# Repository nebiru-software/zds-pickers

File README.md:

# zds-pickers 🎵

Picker controls that are common to ZendrumStudio apps - a React component library for MIDI/music applications.

## Overview

zds-pickers provides a comprehensive set of React components for building MIDI controller interfaces, music applications, and audio configuration UIs. The library focuses on picker-style controls that allow users to select values, notes, channels, and other musical parameters.

## Architecture

The library is organized into several key areas:

- **🎵 Music Components**: Piano interfaces, octave players, and audio providers
- **🎛️ Control Components**: Knobs, sliders, and interactive controls
- **🎯 Selection Components**: Dropdowns and pickers for various MIDI parameters
- **🔧 Utilities**: Shared components and helpers

## Key Features

- **TypeScript-first**: Full type safety with comprehensive interfaces
- **Audio Integration**: Built-in soundfont support for audio feedback
- **MIDI-Focused**: Components designed specifically for MIDI applications
- **Customizable**: Extensive theming and styling options
- **Accessible**: Keyboard navigation and screen reader support
- **Storybook Documentation**: Interactive component playground

## Quick Start

```bash
npm install zds-pickers react-select
```

Peer dependencies (`react`, `react-dom`, `react-select`, `classnames`, `zds-mappings`) must be installed in the host app. `react-select` was moved out of the package bundle in 4.1.x — add it explicitly if you use `Select`-based pickers.

```tsx
import { PianoPicker, KnobPicker, NotePicker } from 'zds-pickers'

function MyMIDIApp() {
  return (
    <div>
      <PianoPicker
        width={800}
        height={200}
        instrumentName="acoustic_grand_piano"
        onChange={(note) => console.log('Note played:', note)}
      />
      <KnobPicker
        label="Volume"
        min={0}
        max={127}
        value={64}
        onChange={(value) => console.log('Volume:', value)}
      />
    </div>
  )
}
```

## Component Documentation

**📚 All component examples, props, and usage patterns are documented in Storybook.**

Run `npm run sb` to access the interactive component playground with:
- Live examples of all components
- Interactive prop controls
- Multiple variants and states
- Copy-paste code snippets

### Available Components

**🎵 Music & Audio**
- `PianoPicker` - Full piano keyboard with soundfont integration
- `OctavePlayer` - Single octave piano interface
- `KeyPicker` - Octave-based MIDI note selection with highlighted key state

**🎛️ Controls**
- `KnobPicker` - Draggable knob with label and value display
- `ResponseCurvePicker` - Visual response curve selection
- `Knob` - Base knob component (from rotaryKnob)

**🎯 Selection**
- `NotePicker` - MIDI note selection with drum mapping support
- `ChannelPicker` - MIDI channel selection (1-16)
- `CCPicker` - MIDI Control Change number selection
- `StatusPicker` - MIDI status message selection
- `ChannelMappingPicker` - Channel mapping with drum kit presets
- `MappingPicker` - General mapping selection
- `PolarityPicker` - On/Off polarity selection
- `LatchPicker` - Latch mode selection
- `ValuePicker` - Generic value selection

**🔧 Utilities**
- `Select` - Generic select component with no-selection support
- `DefaultTooltip` - Tooltip component
- `SvgText` - SVG text rendering

## Audio Integration

The library includes `SoundfontProvider` for audio feedback:

```tsx
<SoundfontProvider
  audioContext={audioContext}
  instrumentName="acoustic_grand_piano"
  soundfont="MusyngKite"
  render={({ isLoading, playNote, stopNote }) => (
    <YourComponent
      playNote={playNote}
      stopNote={stopNote}
      disabled={isLoading}
    />
  )}
/>
```

## Development

### Setup
```bash
npm install
npm run dev          # Start Vite dev server
npm run sb           # Start Storybook
npm run build        # Build library
npm run lint         # Run Biome linter
```

### Storybook
**Primary documentation and testing environment** - all component examples, props, and usage patterns:
```bash
npm run sb
# Opens http://localhost:6006
```

Storybook serves as the single source of truth for:
- Component examples and variants
- Interactive prop controls
- Live code snippets
- Visual testing and development

### Building
The library builds to both CommonJS and ES modules:
- `dist/index.cjs.js` - CommonJS build
- `dist/index.es.js` - ES module build
- `dist/types/` - TypeScript definitions

## Peer dependencies

Install these in your application (they are not bundled with `zds-pickers`):

| Package | Version |
|---------|---------|
| `react` | >=18.0.0 |
| `react-dom` | >=18.0.0 |
| `react-select` | >=5.10.0 |
| `classnames` | >=2.5.1 |
| `zds-mappings` | 1.4.9 |

## Dependencies

### Core Dependencies
- **React 18+** - Component framework (peer)
- **TypeScript** - Type safety
- **D3.js** - Drag interactions and scaling
- **soundfont-player** - Audio playback
- **zds-react-piano** - Piano component
- **zds-mappings** - MIDI mappings

### Development Dependencies
- **Vite** - Build tool
- **Storybook** - Component documentation
- **Biome** - Linting and formatting
- **Tonal** - Music theory utilities

## Type Safety

All components are fully typed with TypeScript. Key interfaces:

```tsx
// Common picker props
interface BasePickerProps {
  disabled?: boolean
  label?: string
  shrinkLabel?: boolean
  value?: number | string
  onChange?: (value: number | string) => void
}

// Audio provider props
interface SoundfontProviderProps {
  audioContext: AudioContext
  instrumentName?: Soundfont.InstrumentName
  soundfont?: 'MusyngKite' | 'FluidR3_GM'
  render: (props: AudioRenderProps) => React.ReactNode
}
```

## Contributing

This is a single-developer library. The codebase follows these patterns:

- **Functional components** with hooks
- **TypeScript interfaces** for all props
- **Storybook stories** for each component
- **Biome** for consistent formatting
- **Modular exports** from index.ts

## License

MIT License - see LICENSE file for details.

## Repository

- **GitHub**: https://github.com/dkadrios/zds-pickers
- **NPM**: https://www.npmjs.com/package/zds-pickers

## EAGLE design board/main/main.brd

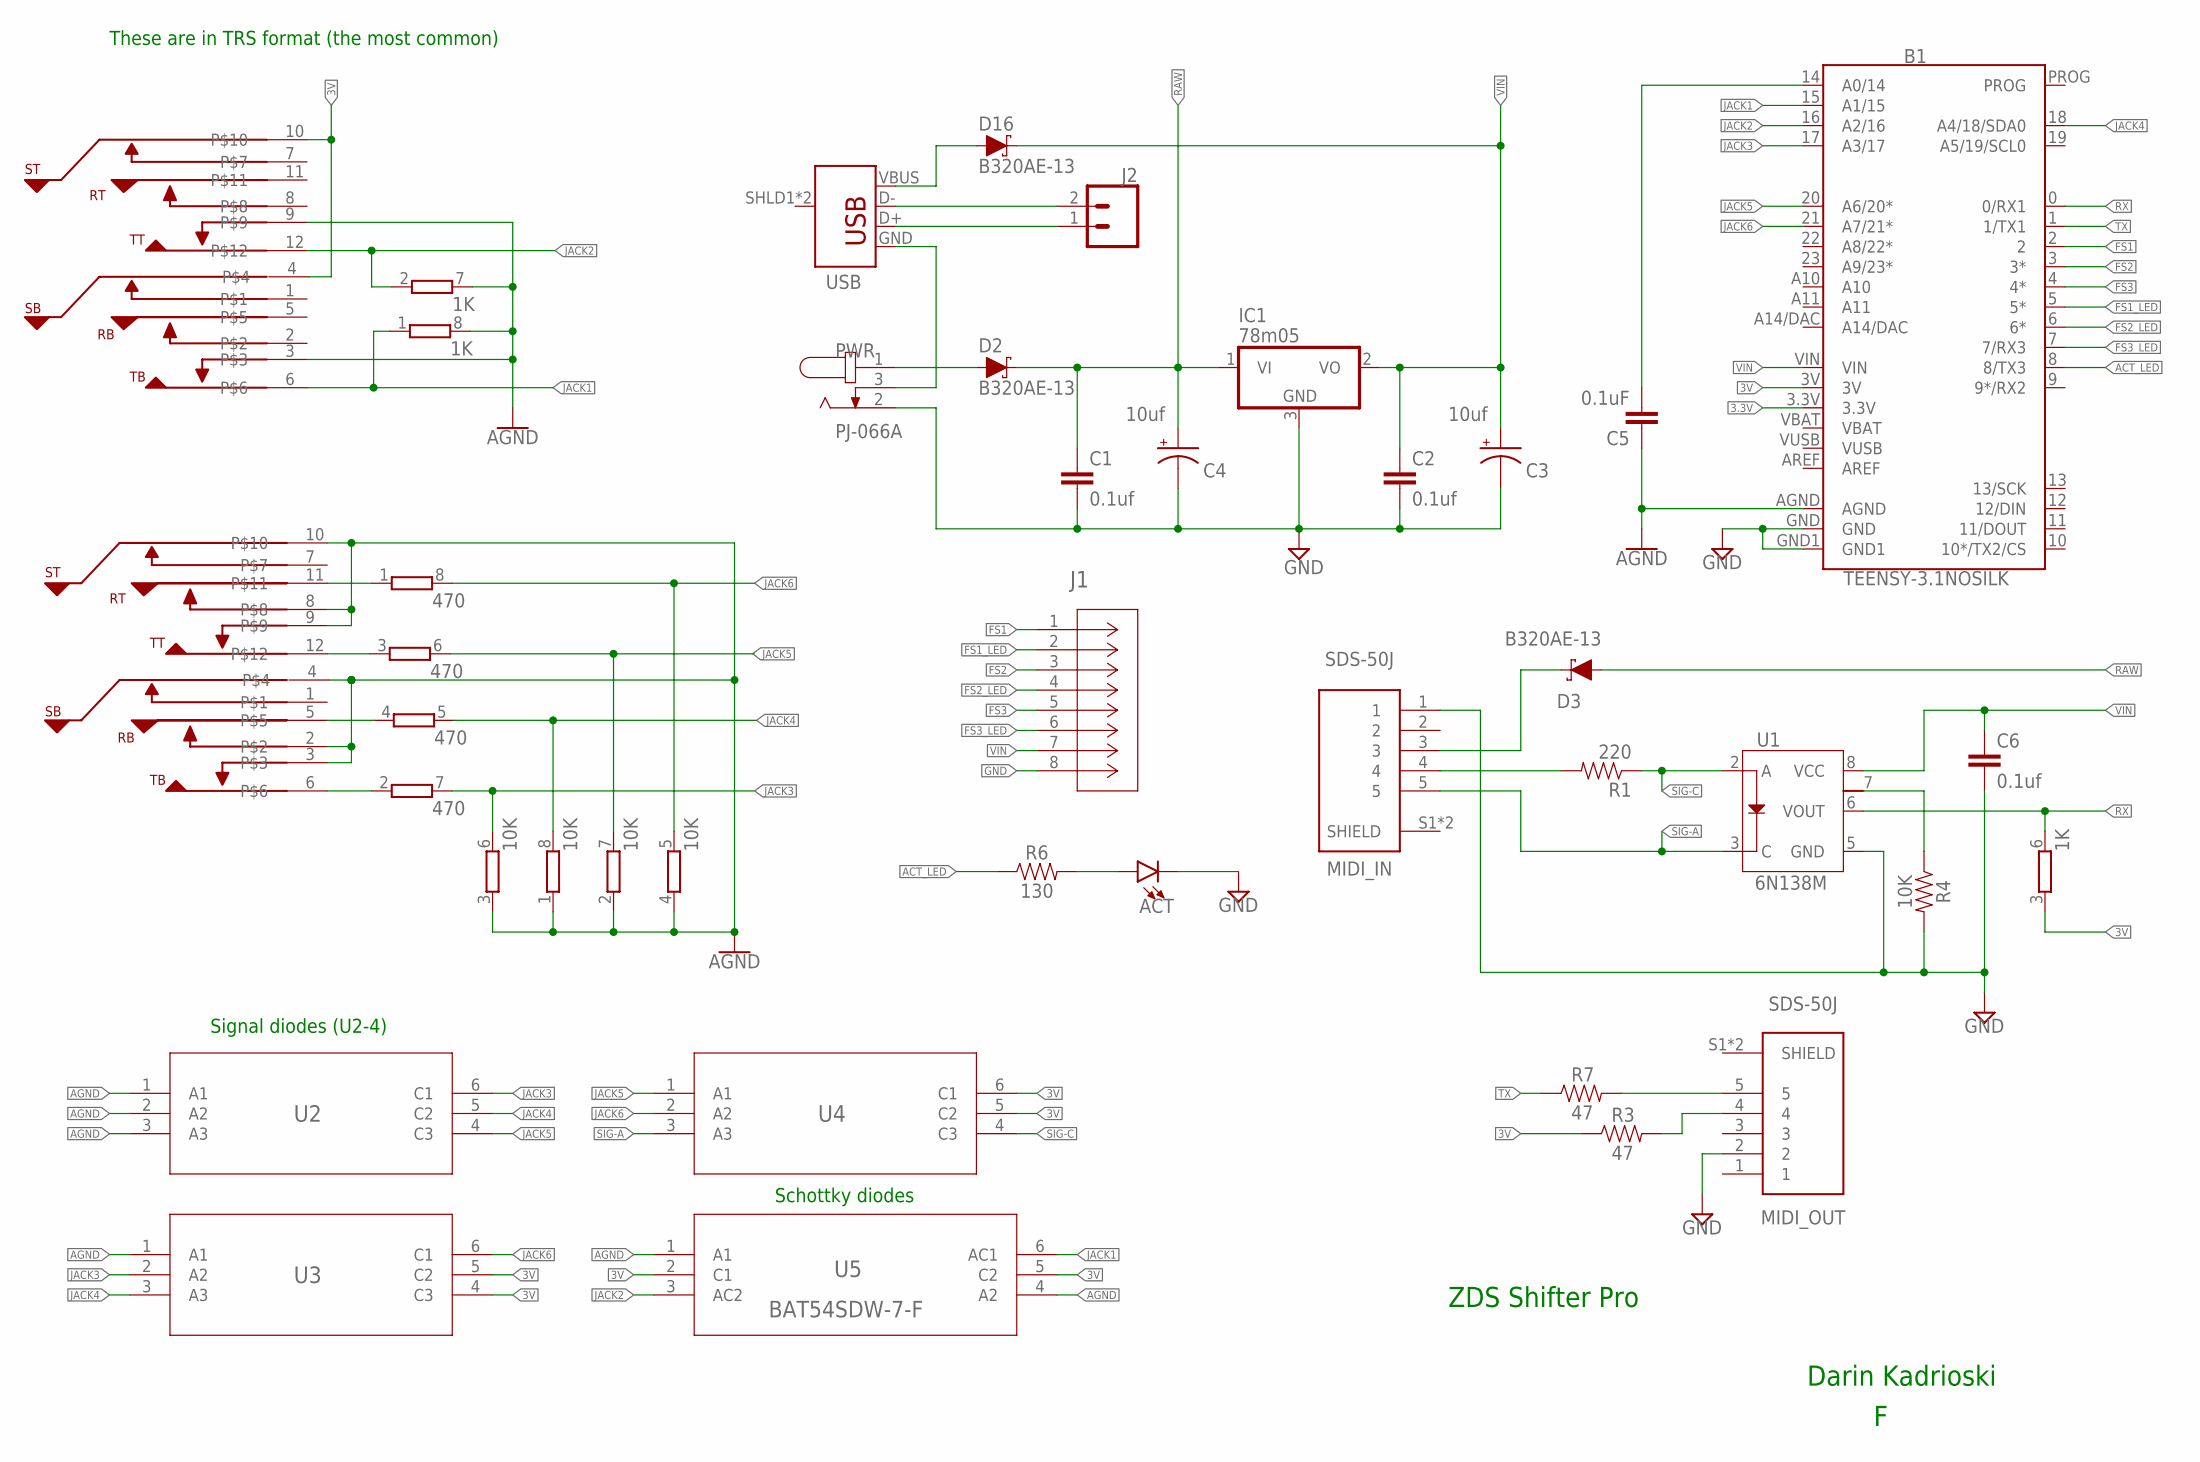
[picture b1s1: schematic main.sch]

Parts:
ACT: LED3MM; LED_3MM
B1: TEENSY-3.1NOSILK; TEENSY-3.1_NOSILK
C1, C2, C6: 0.1uf; C1206
C3, C4: 10uf; PANASONIC_D
C5: 0.1uF; C1206
D2, D3, D16: B320AE-13; SMA-DIODE
EXP: EXP; MHD
IC1: 78m05; TO252
J1: 188275-8; CONN_188275-8_TYC
J2: CONN_02; 1X02
MIDI_IN: SDS-50J; CUI_SDS-50J
MIDI_OUT: SDS-50J; CUI_SDS-50J
PWR: PJ-066A; CUI_PJ-066A
R1: 220; 1206
R3, R7: 47; 1206
R4: 10K; 1206
R6: 130; 1206
RN1: 470; EXB38V
RN2: 10K; EXB38V
RN3: 1K; EXB38V
TRIG1: TRIG; MHD
U1: 6N138M; 8-SMD
U2, U3, U4: MMBD4148TW-7-F; SOT-363_DIO
U5: BAT54SDW-7-F; SOT-363_DIO
USB: USB_B_PTH; USB-B-PTH

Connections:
3.3V: B1.3.3V
3V: B1.3V, EXP.4, EXP.10, R3.1, RN3.3 (1), U3.4 (C3), U3.5 (C2), U4.5 (C2), U4.6 (C1), U5.2 (C1), U5.5 (C2)
ACT_LED: B1.8 (8/TX3), R6.1
AGND: B1.AGND, C5.1, EXP.3, EXP.9, RN2.1, RN2.2 (1), RN2.3 (1), RN2.4 (1), RN3.7 (2), RN3.8 (2), TRIG1.2, TRIG1.3, TRIG1.4, TRIG1.8, TRIG1.9, TRIG1.10, U2.1 (A1), U2.2 (A2), U2.3 (A3), U3.1 (A1), U5.1 (A1), U5.4 (A2)
FS1: B1.2, J1.1
FS1_LED: B1.5 (5*), J1.2
FS2: B1.3 (3*), J1.3
FS2_LED: B1.6 (6*), J1.4
FS3: B1.4 (4*), J1.5
FS3_LED: B1.7 (7/RX3), J1.6
GND: ACT.K (C), B1.GND, B1.GND1, C1.2, C2.2, C3.-, C4.-, C6.2, IC1.3 (GND), J1.8, MIDI_IN.1, MIDI_OUT.2, PWR.2, R4.2, U1.5 (GND)
J3-TIP: RN1.2 (1), TRIG1.6
J4-RING: RN1.4 (1), TRIG1.5
J5-TIP: RN1.3 (1), TRIG1.12
J6-RING: RN1.1, TRIG1.11
JACK1: B1.15 (A1/15), EXP.6, RN3.1, U5.6 (AC1)
JACK2: B1.16 (A2/16), EXP.12, RN3.2 (1), U5.3 (AC2)
JACK3: B1.17 (A3/17), RN1.7 (2), RN2.6 (2), U2.6 (C1), U3.2 (A2)
JACK4: B1.18 (A4/18/SDA0), RN1.5 (2), RN2.8 (2), U2.5 (C2), U3.3 (A3)
JACK5: B1.20 (A6/20*), RN1.6 (2), RN2.7 (2), U2.4 (C3), U4.1 (A1)
JACK6: B1.21 (A7/21*), RN1.8 (2), RN2.5 (2), U3.6 (C1), U4.2 (A2)
unnamed: ACT.A, R6.2
unnamed: MIDI_IN.4, R1.2
unnamed: B1.14 (A0/14), C5.2
unnamed: D3.C, MIDI_IN.3
unnamed: MIDI_OUT.4, R3.2
unnamed: D2.A, PWR.1
unnamed: MIDI_OUT.5, R7.2
unnamed: J2.1, USB.D+
unnamed: R4.1, U1.7
unnamed: J2.2, USB.D-
unnamed: PWR.3, USB.GND
unnamed: D16.A, USB.VBUS
RAW: C1.1, C4.+, D2.C, D3.A, IC1.1 (VI)
RX: B1.0 (0/RX1), RN3.6 (2), U1.6 (VOUT)
SIG-A: MIDI_IN.5, U1.3 (C), U4.3 (A3)
SIG-C: R1.1, U1.2 (A), U4.4 (C3)
TX: B1.1 (1/TX1), R7.1
VBAT: B1.VBAT
VIN: B1.VIN, C2.1, C3.+, C6.1, D16.C, IC1.2 (VO), J1.7, U1.8 (VCC)
VUSB: B1.VUSB

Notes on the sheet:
These are in TRS format (the most common)
Signal diodes (U2-4)
Schottky diodes

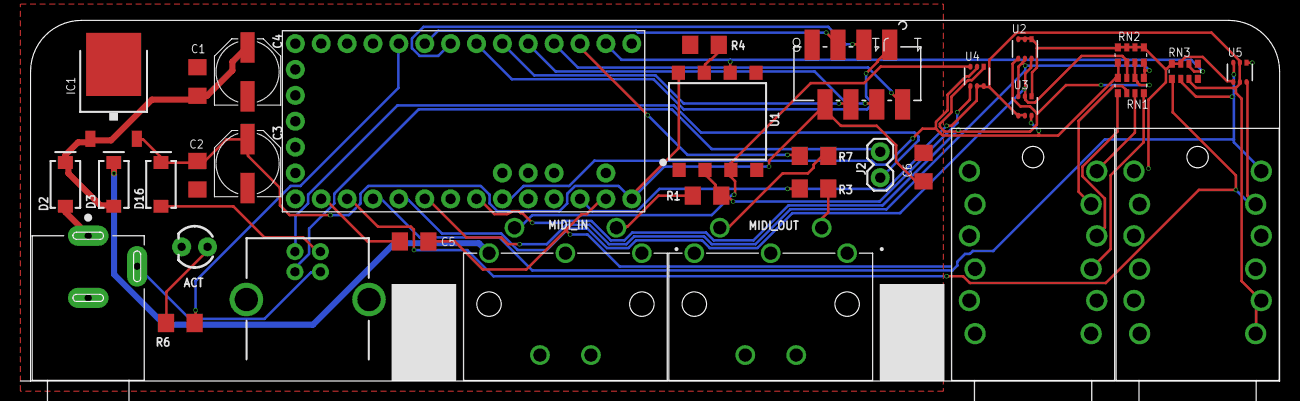
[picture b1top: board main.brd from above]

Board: 2 copper layers, 123.6 x 35.4 mm, 33 parts (0 on the bottom side), 38 nets.

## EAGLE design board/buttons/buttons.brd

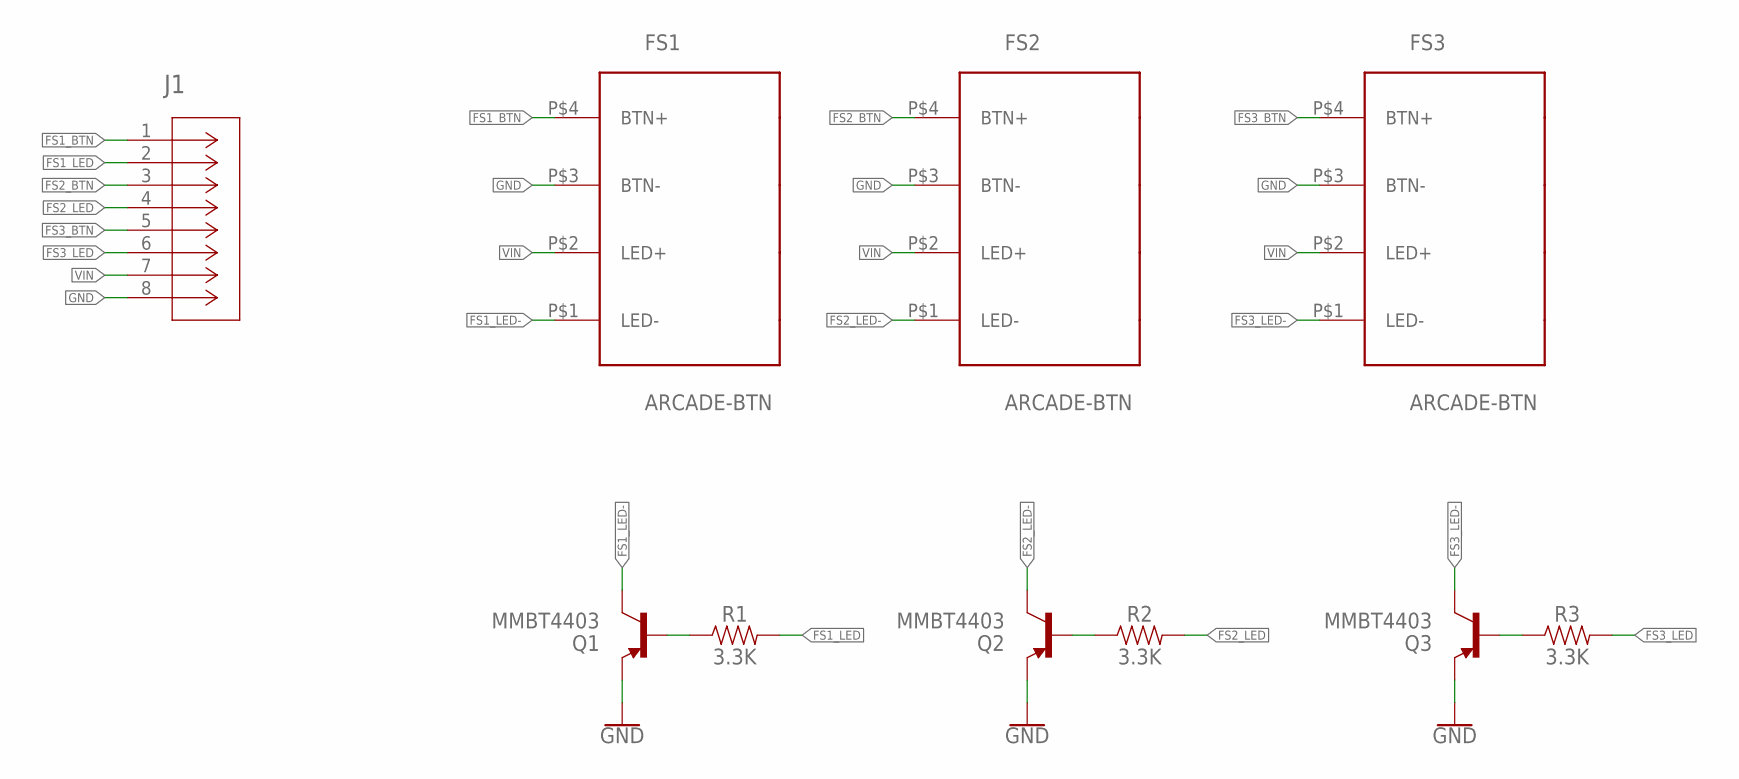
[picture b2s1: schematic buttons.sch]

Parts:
FS1, FS2, FS3: ARCADE-BTN
J1: 188275-8; CONN_188275-8_TYC
Q1, Q2, Q3: MMBT4403; SOT23-3
R1, R2, R3: 3.3K; 1206

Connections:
FS1_BTN: FS1.P$4 (BTN+), J1.1
FS1_LED: J1.2, R1.2
FS1_LED-: FS1.P$1 (LED-), Q1.3 (C)
FS2_BTN: FS2.P$4 (BTN+), J1.3
FS2_LED: J1.4, R2.2
FS2_LED-: FS2.P$1 (LED-), Q2.3 (C)
FS3_BTN: FS3.P$4 (BTN+), J1.5
FS3_LED: J1.6, R3.2
FS3_LED-: FS3.P$1 (LED-), Q3.3 (C)
GND: FS1.P$3 (BTN-), FS2.P$3 (BTN-), FS3.P$3 (BTN-), J1.8, Q1.2 (E), Q2.2 (E), Q3.2 (E)
unnamed: Q1.1 (B), R1.1
unnamed: Q3.1 (B), R3.1
unnamed: Q2.1 (B), R2.1
VIN: FS1.P$2 (LED+), FS2.P$2 (LED+), FS3.P$2 (LED+), J1.7

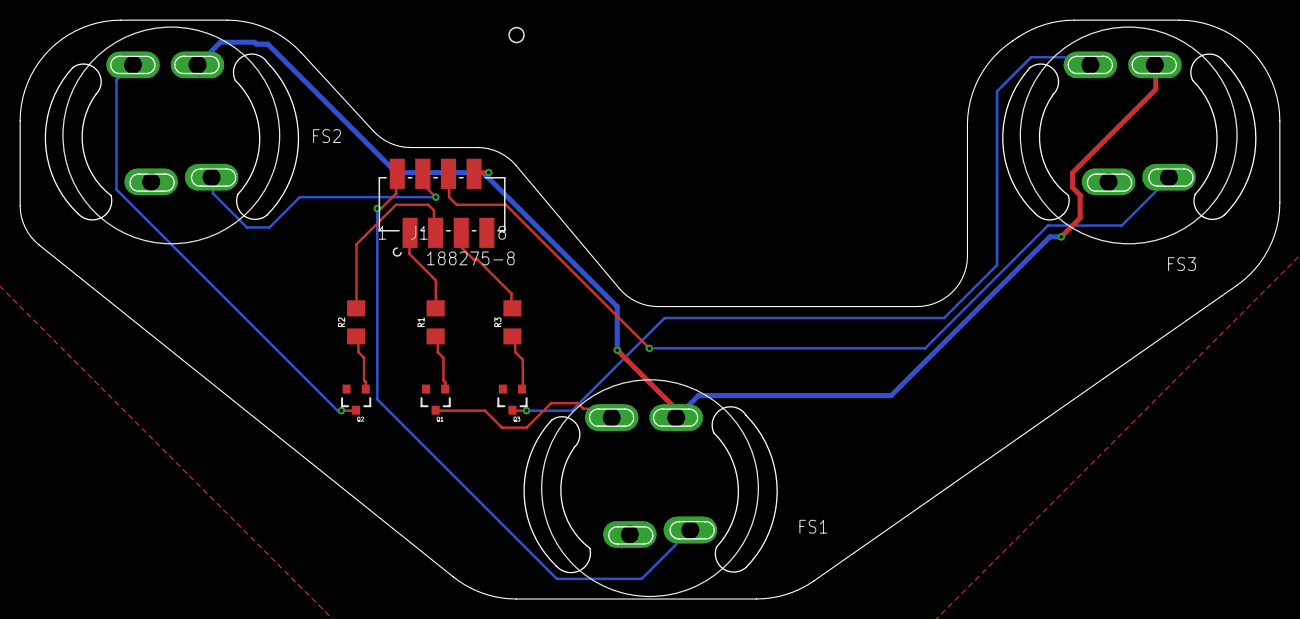
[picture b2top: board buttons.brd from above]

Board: 2 copper layers, 125.0 x 57.4 mm, 10 parts (0 on the bottom side), 14 nets.

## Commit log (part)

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2017-12-30 Moving additional controls from other projects.
2018-04-15 Updating packages. Passing through more properties to pickers. eslint was not working. correcting issues
2018-04-19 ValuePicker must implement React.Component in order to receive a ref
2018-04-19 adopting material-ui's inputRef func
2018-04-19 omit needs strings
2018-04-22 Omit 'classes' from passthrough
2018-05-12 v1.1.12
2018-05-13 v1.1.14
2018-05-13 v1.1.16
2018-05-14 Updating notepicker so that it works with zds-mappings
2018-05-14 v1.2.0
2018-05-16 v1.2.1
2018-05-16 export cc values
2018-06-01 MenuItem path changed
2018-07-25 Adding some tests
2018-10-07 updating babel
2018-10-08 focusing notepickers
2018-10-10 always render available note entries
2018-11-18 Updating material-ui and other packages
2019-01-06 replace note picker with react-select package updates
2019-01-14 removing internal styling -- consumer will be responsible for all styles
2019-06-02 fix dependancy
2019-11-02 Bump eslint-utils from 1.3.1 to 1.4.3
    Bumps [eslint-utils](https://github.com/mysticatea/eslint-utils) from 1.3.1 to 1.4.3.
    - [Release notes](https://github.com/mysticatea/eslint-utils/releases)
    - [Commits](https://github.com/mysticatea/eslint-utils/compare/v1.3.1...v1.4.3)
2020-03-13 Bump acorn from 5.7.3 to 5.7.4
    Bumps [acorn](https://github.com/acornjs/acorn) from 5.7.3 to 5.7.4.
    - [Release notes](https://github.com/acornjs/acorn/releases)
    - [Commits](https://github.com/acornjs/acorn/compare/5.7.3...5.7.4)
2020-08-29 initial checkin
2020-08-29 formatting
2020-08-29 addressing issues that cppcheck found
2020-09-05 don't track backups
2020-09-05 pedals are close to done
2020-09-07 schematic updates
2020-09-12 updating components
2020-10-10 client checkin
2020-10-11 beginning to convert styles
    shifter is still not being detected
2020-10-18 refactoring board
    moving to stacked 1/4 jacks to reduce board width
    switching to resistor networks and diode arrays to shrink footprint and make assembly a bit easier
2020-11-07 board changes
2020-11-09 still refactoring
2020-11-17 updated hole template
2020-11-20 graphics
2020-12-07 touched eagle files
2020-12-13 client handshake working
2020-12-13 complete upgrade to react 17
2020-12-13 getting user info working
2020-12-14 leds
2020-12-15 updating to use the newer react-select
2020-12-15 Bump ini from 1.3.5 to 1.3.8
    Bumps [ini](https://github.com/isaacs/ini) from 1.3.5 to 1.3.8.
    - [Release notes](https://github.com/isaacs/ini/releases)
    - [Commits](https://github.com/isaacs/ini/compare/v1.3.5...v1.3.8)
2020-12-16 Bump lodash from 4.17.15 to 4.17.20
    Bumps [lodash](https://github.com/lodash/lodash) from 4.17.15 to 4.17.20.
    - [Release notes](https://github.com/lodash/lodash/releases)
    - [Commits](https://github.com/lodash/lodash/compare/4.17.15...4.17.20)
2020-12-16 handleChange
2020-12-16 export settings
2020-12-18 user mappings
2020-12-18 remove sass
2020-12-18 better logo
2020-12-19 tweaking layout
2020-12-20 adding basis for jack controls
2020-12-22 adding calibration controls
2020-12-30 latest version 3.2.x
2020-12-31 Bump minimist from 1.2.0 to 1.2.5
    Bumps [minimist](https://github.com/substack/minimist) from 1.2.0 to 1.2.5.
    - [Release notes](https://github.com/substack/minimist/releases)
    - [Commits](https://github.com/substack/minimist/compare/1.2.0...1.2.5)
2021-01-01 v3.2.7
2021-01-01 v3.2.9
2021-01-01 adding channel mapping picker
2021-01-01 better formatting
2021-01-02 notepicker onchange was not firing
2021-04-10 cleanup
2021-04-17 valuepicker
2021-05-17 all pickers can shrink the label; value picker is now just a select
2021-06-17 Bump postcss from 7.0.35 to 7.0.36
    Bumps [postcss](https://github.com/postcss/postcss) from 7.0.35 to 7.0.36.
    - [Release notes](https://github.com/postcss/postcss/releases)
    - [Changelog](https://github.com/postcss/postcss/blob/main/CHANGELOG.md)
    - [Commits](https://github.com/postcss/postcss/compare/7.0.35...7.0.36)
    ---
    updated-dependencies:
2021-08-03 Bump tar from 6.1.0 to 6.1.3
    Bumps [tar](https://github.com/npm/node-tar) from 6.1.0 to 6.1.3.
    - [Release notes](https://github.com/npm/node-tar/releases)
    - [Changelog](https://github.com/npm/node-tar/blob/main/CHANGELOG.md)
    - [Commits](https://github.com/npm/node-tar/compare/v6.1.0...v6.1.3)
    ---
    updated-dependencies:
2021-08-11 Bump path-parse from 1.0.6 to 1.0.7
    Bumps [path-parse](https://github.com/jbgutierrez/path-parse) from 1.0.6 to 1.0.7.
    - [Release notes](https://github.com/jbgutierrez/path-parse/releases)
    - [Commits](https://github.com/jbgutierrez/path-parse/commits/v1.0.7)
    ---
    updated-dependencies:
    - dependency-name: path-parse
2021-08-13 allowing numbers to go highToLow
2021-08-15 adding knobs
2021-08-15 helps if you export it
2021-08-15 ability to hide knob label
2021-08-15 Bump tar from 6.1.0 to 6.1.8
    Bumps [tar](https://github.com/npm/node-tar) from 6.1.0 to 6.1.8.
    - [Release notes](https://github.com/npm/node-tar/releases)
    - [Changelog](https://github.com/npm/node-tar/blob/main/CHANGELOG.md)
    - [Commits](https://github.com/npm/node-tar/compare/v6.1.0...v6.1.8)
    ---
    updated-dependencies:
2021-08-16 need a classname to target
2021-09-26 removing dependency on external skin pack for knobs
2021-09-26 Bump tar from 6.1.8 to 6.1.11 (#14)
    Bumps [tar](https://github.com/npm/node-tar) from 6.1.8 to 6.1.11.
    - [Release notes](https://github.com/npm/node-tar/releases)
    - [Changelog](https://github.com/npm/node-tar/blob/main/CHANGELOG.md)
    - [Commits](https://github.com/npm/node-tar/compare/v6.1.8...v6.1.11)
    ---
    updated-dependencies:
2021-10-03 explicitly importing React for projects that still require it
2021-10-04 trying some stuff
2021-10-11 when using groups, initial value was not selected
2022-04-10 Bump minimist from 1.2.5 to 1.2.6
    Bumps [minimist](https://github.com/substack/minimist) from 1.2.5 to 1.2.6.
    - [Release notes](https://github.com/substack/minimist/releases)
    - [Commits](https://github.com/substack/minimist/compare/1.2.5...1.2.6)
    ---
    updated-dependencies:
    - dependency-name: minimist
2022-07-21 Bump terser from 4.8.0 to 4.8.1
    Bumps [terser](https://github.com/terser/terser) from 4.8.0 to 4.8.1.
    - [Release notes](https://github.com/terser/terser/releases)
    - [Changelog](https://github.com/terser/terser/blob/master/CHANGELOG.md)
    - [Commits](https://github.com/terser/terser/commits)
    ---
    updated-dependencies:
2022-08-03 Bump node-fetch from 2.6.1 to 2.6.7 (#17)
    Bumps [node-fetch](https://github.com/node-fetch/node-fetch) from 2.6.1 to 2.6.7.
    - [Release notes](https://github.com/node-fetch/node-fetch/releases)
    - [Commits](https://github.com/node-fetch/node-fetch/compare/v2.6.1...v2.6.7)
    ---
    updated-dependencies:
    - dependency-name: node-fetch
2022-08-05 SVG Text now needs default coords
2022-10-22 supporting react 18
2022-10-23 could not open response picker
2022-11-17 Bump loader-utils from 1.4.0 to 1.4.2
    Bumps [loader-utils](https://github.com/webpack/loader-utils) from 1.4.0 to 1.4.2.
    - [Release notes](https://github.com/webpack/loader-utils/releases)
    - [Changelog](https://github.com/webpack/loader-utils/blob/v1.4.2/CHANGELOG.md)
    - [Commits](https://github.com/webpack/loader-utils/compare/v1.4.0...v1.4.2)
    ---
    updated-dependencies:
2023-01-02 bump version
2023-01-07 Bump json5 from 1.0.1 to 1.0.2
    Bumps [json5](https://github.com/json5/json5) from 1.0.1 to 1.0.2.
    - [Release notes](https://github.com/json5/json5/releases)
    - [Changelog](https://github.com/json5/json5/blob/main/CHANGELOG.md)
    - [Commits](https://github.com/json5/json5/compare/v1.0.1...v1.0.2)
    ---
    updated-dependencies:
2023-01-16 adding piano picker
2023-01-16 forked react-piano
2023-01-16 bumped piano
2023-01-28 guard against missing status types
2023-11-19 upgrade storybook
2023-12-05 add melodic mode to note picker
2025-01-16 move to vite
2025-01-17 getting stories working
2025-01-18 good enough for v1
2025-01-18 preparing to publish
2025-01-19 typing status picker
2025-01-20 knob kinda works
2025-01-22 completing the upgrade
2025-01-22 Fix casing issue for SvgText
2025-01-28 notepicker action button wasn't working
2025-03-04 vertical slider (#25)
    * notepicker action button wasn't working
    * making sure all pickers support "no selection"
2025-03-04 nested options problem
2025-03-25 Bump vite from 6.2.0 to 6.2.3
    Bumps [vite](https://github.com/vitejs/vite/tree/HEAD/packages/vite) from 6.2.0 to 6.2.3.
    - [Release notes](https://github.com/vitejs/vite/releases)
    - [Changelog](https://github.com/vitejs/vite/blob/v6.2.3/packages/vite/CHANGELOG.md)
    - [Commits](https://github.com/vitejs/vite/commits/v6.2.3/packages/vite)
    ---
    updated-dependencies:
2025-04-04 Bump vite from 6.2.0 to 6.2.5
    Bumps [vite](https://github.com/vitejs/vite/tree/HEAD/packages/vite) from 6.2.0 to 6.2.5.
    - [Release notes](https://github.com/vitejs/vite/releases)
    - [Changelog](https://github.com/vitejs/vite/blob/v6.2.5/packages/vite/CHANGELOG.md)
    - [Commits](https://github.com/vitejs/vite/commits/v6.2.5/packages/vite)
    ---
    updated-dependencies:
2025-04-30 Bump vite from 6.2.0 to 6.3.4
    Bumps [vite](https://github.com/vitejs/vite/tree/HEAD/packages/vite) from 6.2.0 to 6.3.4.
    - [Release notes](https://github.com/vitejs/vite/releases)
    - [Changelog](https://github.com/vitejs/vite/blob/main/packages/vite/CHANGELOG.md)
    - [Commits](https://github.com/vitejs/vite/commits/v6.3.4/packages/vite)
    ---
    updated-dependencies:
2025-09-12 Update package versions and enhance documentation
    - Bump version to 4.0.26 in package.json and 4.0.25 in package-lock.json.
    - Update tonal dependency to version 6.4.2.
    - Revise README.md to provide a comprehensive overview of the zds-pickers library, including architecture, key features, quick start guide, and component documentation.
    - Refactor Vite configuration to include additional external dependencies.
    - Introduce global MIDI object handling in SoundFontProvider for better compatibility.
    - Clean up KeyPicker component implementation and update stories to include KeyPicker example.
2025-09-12 Refactor OctavePlayer and KeyPicker components to remove startNote prop
    - Remove startNote prop from OctavePlayer and KeyPicker components for simplification.
    - Update logic to default to the first note in the baseNotes array for note calculations.
    - Adjust KeyPicker to calculate octave range without startNote.
    - Clean up related stories by removing examples that utilized startNote.
2025-09-13 Update version to 4.1.4 and enhance soundfont handling
    - Bump version to 4.1.4 in package.json.
    - Update sideEffects and files properties to include soundfont directories.
    - Implement a Vite plugin to copy soundfonts to the dist directory after build.
    - Refactor SoundFontProvider to import soundfonts correctly and improve audio context handling.
    - Add acoustic grand piano soundfont file to the library.
2026-05-29 Update dependencies and improve documentation for zds-pickers
    - Bump version to 4.1.4 in package.json and package-lock.json.
    - Update Storybook and React dependencies to version 8.6.18.
    - Add storybook-static to .gitignore to prevent unnecessary files from being tracked.
    - Revise README.md to clarify peer dependencies and installation instructions for `react-select`.
    - Refactor OctavePlayer and PianoPicker components to utilize new type definitions for better type safety.
    - Clean up code formatting and improve error handling in SoundFontProvider.
2026-05-30 Up1 parity for pickers (#34)
    * Update package versions and add KeyPicker component
    - Bump version to 4.0.25 in package.json and package-lock.json.
    - Update dependencies including caniuse-lite and vite.
    - Introduce KeyPicker component to the library, allowing selection of musical keys.
    - Modify OctavePlayer and PianoPicker to support new KeyPicker functionality.
    - Update stories to include KeyPicker example.
2026-05-30 npm vulnerabilities
2026-05-30 pushed version 4.1.6
2026-05-30 small fix (#35)
    * npm vulnerabilities
    * Revert "npm vulnerabilities"
    This reverts commit 3d2a4eab20c571dff3c1103bffce7c9ca6b4ca08.
    * pushed version 4.1.6
    * npm cleanup

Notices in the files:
parts and their libraries:
User-Submitted: Licensing: Creative Commons ShareAlike 4.0 International - https://creativecommons.org/licenses/by-sa/4.0
COPYRIGHT: Copyright (C) 2016 Accelerated Designs. All rights reserved
